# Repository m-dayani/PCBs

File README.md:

# PCBs

A collection of previous PCB designs

## CPLD Development Board

## Logic Circuits

### Logic Gates

### Combinational Logic

### Sequential Logic - Latch/FF

### Sequential Logic - SReg/Counter

## Miscellaneous

### Power Supply

### Tiny Oscilloscope

## Dependencies

These designs are tested using the following sotfware:

- Altium Designer 16.0.8 2015
- Eagle 7.6.0

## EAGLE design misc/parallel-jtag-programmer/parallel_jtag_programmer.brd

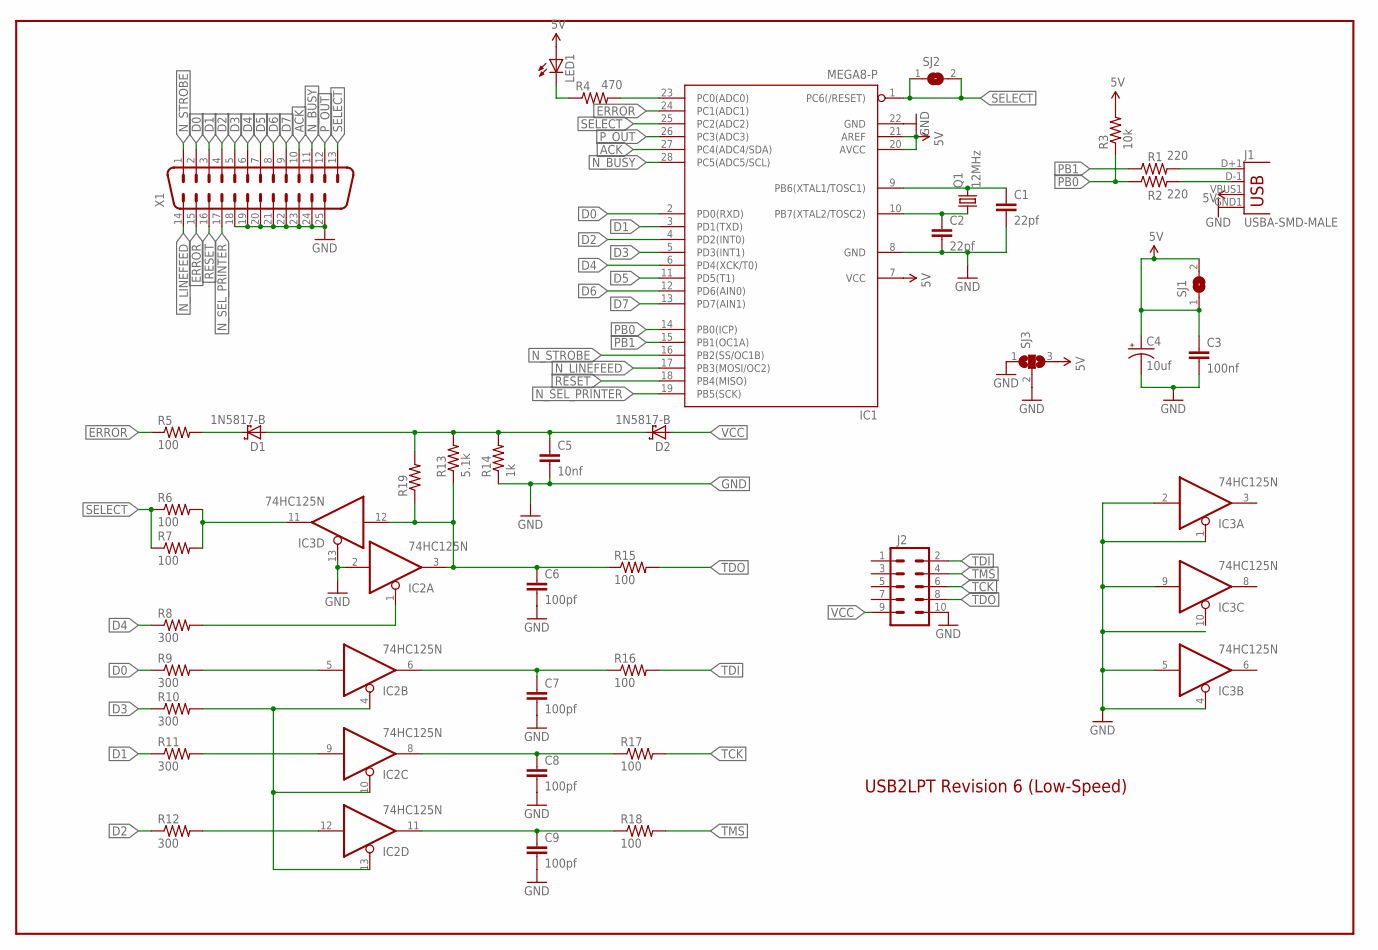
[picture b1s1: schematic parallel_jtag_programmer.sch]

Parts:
C1, C2: 22pf; CAP-PTH-SMALL
C3: 100nf; CAP-PTH-5MM
C4: 10uf; CPOL-RADIAL-10UF-25V
C5: 10nf; CAP-PTH-SMALL
C6, C7, C8, C9: 100pf; CAP-PTH-5MM
D1, D2: 1N5817-B; DO41-7.6
IC1: MEGA8-P; DIL28-3
IC2, IC3: 74HC125N; DIL14
J1: USBA-SMD-MALE; USB-A-SMT-MALE
J2: M05X2SHD; 2X5-SHROUDED
LED1: LED3MM
Q1: 12MHz; HC49U-V
R1, R2: 220; AXIAL-0.3
R3: 10k; AXIAL-0.3
R4: 470; AXIAL-0.3
R5, R6, R7, R15, R16, R17, R18: 100; AXIAL-0.3
R8, R9, R10, R11, R12: 300; AXIAL-0.3
R13: 5.1k; AXIAL-0.3
R14: 1k; AXIAL-0.3
R19: RESISTORAXIAL-0.3; AXIAL-0.3
SJ1, SJ2: SJ
SJ3: SJ2W; SJ_2
X1: DB25H; M25H

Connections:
5V: C3.1, C4.1 (+), IC1.7 (VCC), IC1.20 (AVCC), IC1.21 (AREF), J1.VBUS1 (VBUS), LED1.A, R3.P$2 (2), SJ1.1, SJ1.2, SJ3.3
ACK: IC1.27 (PC4(ADC4/SDA)), X1.10
D0: IC1.2 (PD0(RXD)), R9.P$1 (1), X1.2
D1: IC1.3 (PD1(TXD)), R11.P$1 (1), X1.3
D2: IC1.4 (PD2(INT0)), R12.P$1 (1), X1.4
D3: IC1.5 (PD3(INT1)), R10.P$1 (1), X1.5
D4: IC1.6 (PD4(XCK/T0)), R8.P$1 (1), X1.6
D5: IC1.11 (PD5(T1)), X1.7
D6: IC1.12 (PD6(AIN0)), X1.8
D7: IC1.13 (PD7(AIN1)), X1.9
ERROR: IC1.24 (PC1(ADC1)), R5.P$1 (1), X1.15
GND: C1.2, C2.2, C3.2, C4.2 (-), C5.2, C6.2, C7.2, C8.2, C9.2, IC1.8 (GND), IC1.22 (GND), IC2.2 (I), IC2.7 (GND), IC3.1 (OE), IC3.2 (I), IC3.4 (OE), IC3.5 (I), IC3.7 (GND), IC3.9 (I), IC3.13 (OE), J1.GND1 (GND), J2.10, R14.P$1 (1), SJ3.1, SJ3.2, X1.18, X1.19, X1.20, X1.21, X1.22, X1.23, X1.24, X1.25
unnamed: LED1.K (C), R4.P$1 (1)
unnamed: IC1.23 (PC0(ADC0)), R4.P$2 (2)
unnamed: C5.1, D1.A, D2.C, R13.P$2 (2), R14.P$2 (2), R19.P$2 (2)
unnamed: C2.1, IC1.10 (PB7(XTAL2/TOSC2)), Q1.1
unnamed: C1.1, IC1.9 (PB6(XTAL1/TOSC1)), Q1.2
unnamed: J1.D-1 (D-), R2.P$2 (2)
unnamed: J1.D+1 (D+), R1.P$2 (2)
unnamed: C6.1, IC2.3 (O), IC3.12 (I), R13.P$1 (1), R15.P$1 (1), R19.P$1 (1)
unnamed: IC2.1 (OE), R8.P$2 (2)
unnamed: IC3.11 (O), R6.P$2 (2), R7.P$2 (2)
unnamed: IC2.5 (I), R9.P$2 (2)
unnamed: IC2.4 (OE), IC2.10 (OE), IC2.13 (OE), R10.P$2 (2)
unnamed: D1.C, R5.P$2 (2)
unnamed: C7.1, IC2.6 (O), R16.P$1 (1)
unnamed: C8.1, IC2.8 (O), R17.P$1 (1)
unnamed: IC2.9 (I), R11.P$2 (2)
unnamed: IC2.12 (I), R12.P$2 (2)
unnamed: C9.1, IC2.11 (O), R18.P$1 (1)
N_BUSY: IC1.28 (PC5(ADC5/SCL)), X1.11
N_LINEFEED: IC1.17 (PB3(MOSI/OC2)), X1.14
N_SEL_PRINTER: IC1.19 (PB5(SCK)), X1.17
N_STROBE: IC1.16 (PB2(SS/OC1B)), X1.1
PB0: IC1.14 (PB0(ICP)), R2.P$1 (1), R3.P$1 (1)
PB1: IC1.15 (PB1(OC1A)), R1.P$1 (1)
P_OUT: IC1.26 (PC3(ADC3)), X1.12
RESET: IC1.18 (PB4(MISO)), X1.16
SELECT: IC1.1 (PC6(/RESET)), IC1.25 (PC2(ADC2)), R6.P$1 (1), R7.P$1 (1), SJ2.1, SJ2.2, X1.13
TCK: J2.6
TDI: J2.2, R16.P$2 (2)
TDO: J2.8, R15.P$2 (2)
TMS: J2.4, R18.P$2 (2)
VCC: D2.A, IC2.14 (VCC), IC3.14 (VCC), J2.9

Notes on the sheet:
USB2LPT Revision 6 (Low-Speed)

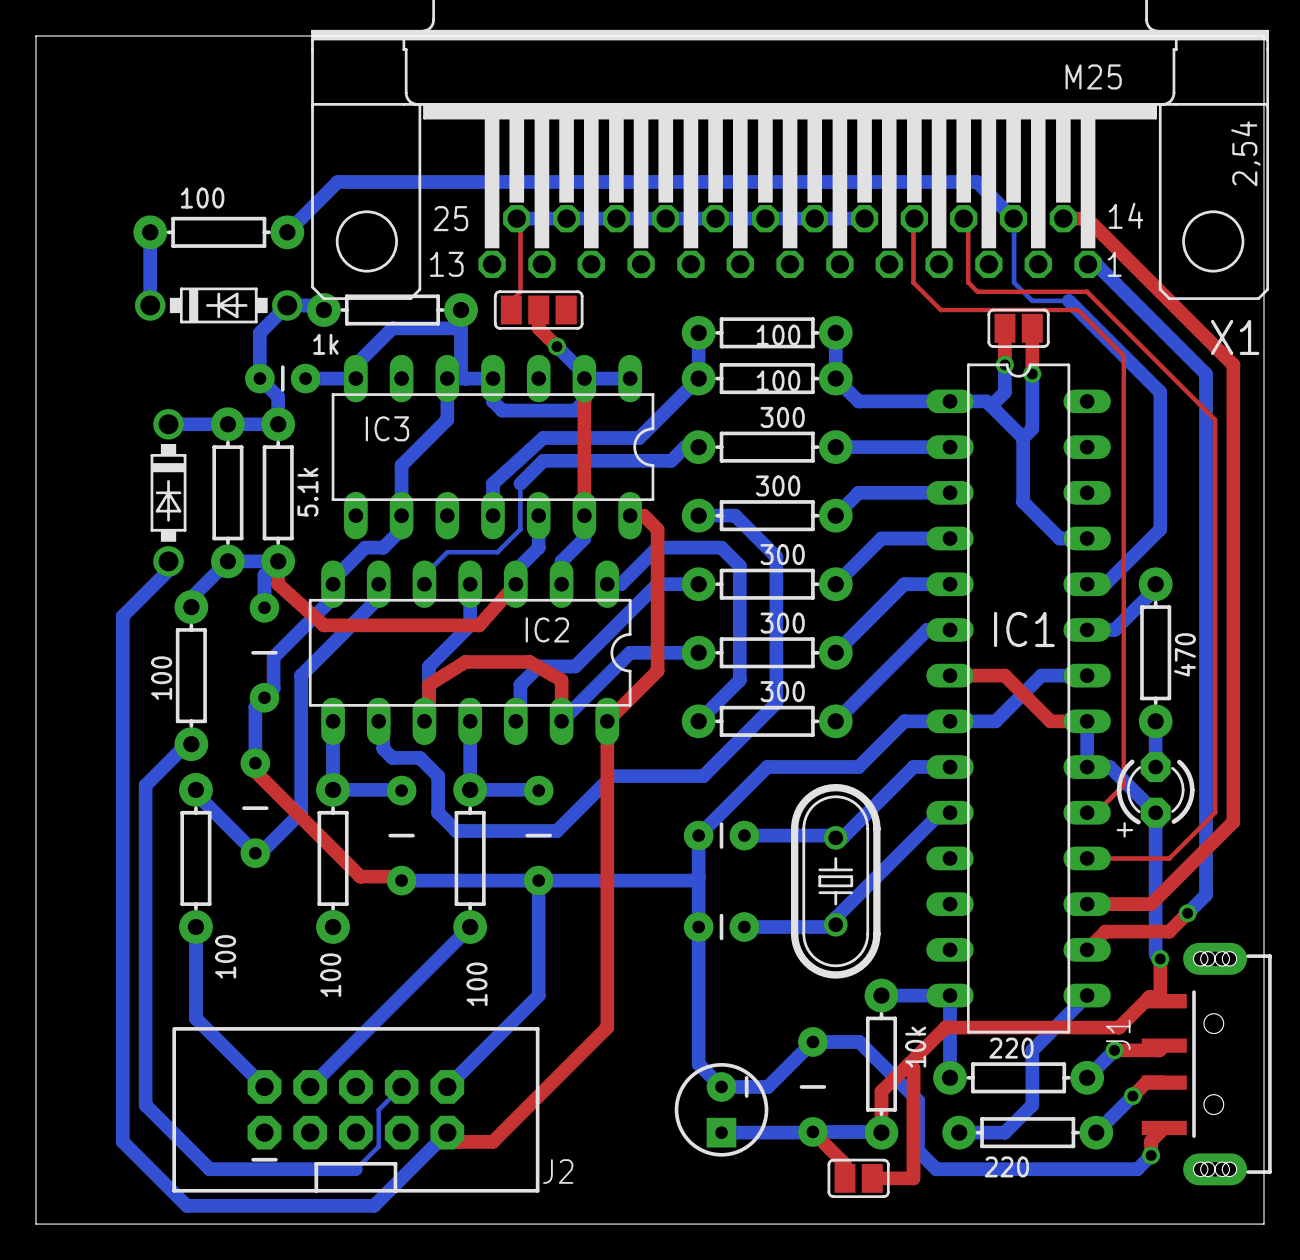
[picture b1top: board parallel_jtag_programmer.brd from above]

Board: 2 copper layers, 68.2 x 66.0 mm, 41 parts (0 on the bottom side), 43 nets.

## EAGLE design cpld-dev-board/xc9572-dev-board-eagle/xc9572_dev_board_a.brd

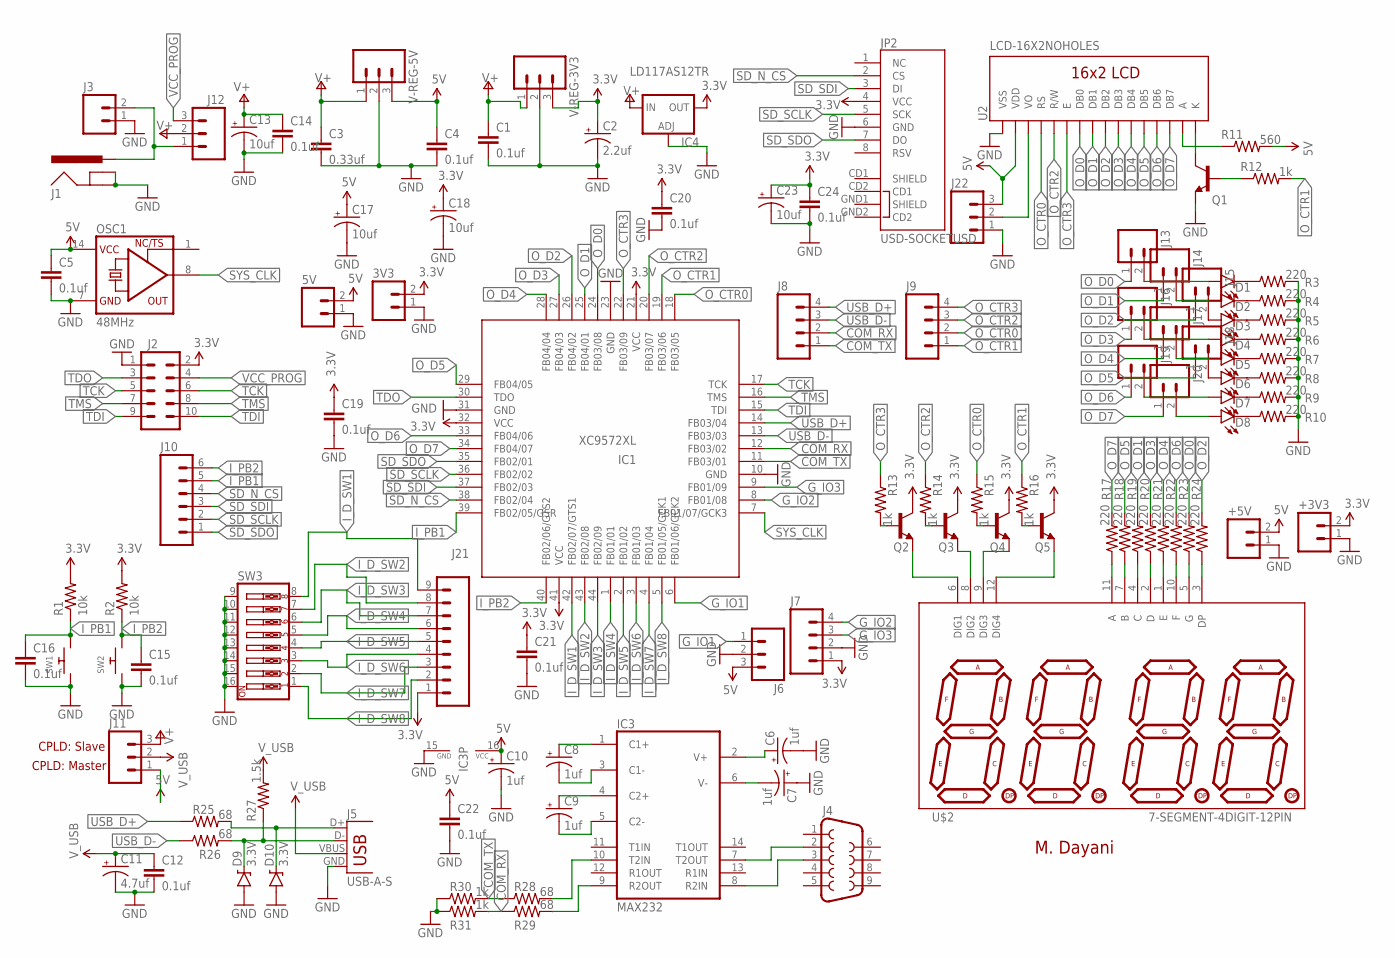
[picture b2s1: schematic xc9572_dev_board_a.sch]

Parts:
3V3, 5V: M02PTH; 1X02
+3V3, +5V: M02JST-PTH-VERT; JST-2-PTH-VERT
C1, C4, C5, C12, C14, C15, C16, C19, C20, C21, C22, C24: 0.1uf; 1206
C2: 2.2uf; EIA3216
C3: 0.33uf; 1206
C6, C7, C8, C9, C10: 1uf; EIA3216
C11: 4.7uf; EIA3216
C13, C17, C18, C23: 10uf; EIA3216
D1, D2, D3, D4, D5, D6, D7, D8: LED1206; LED-1206
D9, D10: 3.3V; SOD-323
IC1: XC9572XL; PLCC-S44
IC3: MAX232; DIL16
IC4: LD117AS12TR; SOT223
J1: POWER_JACKPTH_BREAD; POWER_JACK_PTH_BREAD
J2: M05X2SHD; 2X5-SHROUDED
J3: M02JST-PTH-VERT; JST-2-PTH-VERT
J4: DB9FEMALE; DB9
J5: USB-A-S
J6, J11, J12: M03PTH; 1X03
J7, J8, J9: M04PTH; 1X04
J10: M06SILK_FEMALE_PTH; 1X06
J13, J14, J15, J16, J17, J18, J19, J20: M02PTH; 1X02
J21: M09; 1X09
J22: M03POLAR; MOLEX-1X3
JP2: USD-SOCKETUSD; USD-SOCKET-PP
OSC1: 48MHz; DIL14S
Q1, Q2, Q3, Q4, Q5: TRANSISTOR_NPNSOT23-3; SOT23-3
R1, R2: 10k; 1206
R3, R4, R5, R6, R7, R8, R9, R10, R17, R18, R19, R20, R21, R22, R23, R24: 220; 1206
R11: 560; 1206
R12, R13, R14, R15, R16, R30, R31: 1k; 1206
R25, R26, R28, R29: 68; 1206
R27: 1.5k; 1206
SW1, SW2: SWITCH_PUSHBUTTONEVQ-PE; TACT_PANA-EVQ
SW3: SW_DIP-8; DIPSWITCH-08
U2: LCD-16X2NOHOLES; LCD-16X2_NOHOLES
U$2: 7-SEGMENT-4DIGIT-12PIN; 7-SEGMENT-4DIGIT-12PIN-LONGPADS
V-REG-3V3, V-REG-5V: M03PTH; 1X03

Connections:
3.3V: 3V3.2, +3V3.2, C2.A (+), C18.A (+), C19.1, C20.1, C21.1, C23.A (+), C24.1, IC1.21 (VCC), IC1.32 (VCC), IC1.41 (VCC), IC4.4 (OUT), J2.2, J7.1, J21.1, JP2.4 (VCC), Q2.3 (C), Q3.3 (C), Q4.3 (C), Q5.3 (C), R1.2, R2.2, V-REG-3V3.3
5V: 5V.2, +5V.2, C4.1, C5.1, C10.A (+), C17.A (+), C22.1, IC3.16 (VCC), J6.3, J11.1, J22.3, OSC1.14 (VCC), R11.2, U2.2 (VDD), V-REG-5V.3
COM_RX: IC1.12 (FB03/02), J8.2, R29.1, R31.2
COM_TX: IC1.11 (FB03/01), J8.1, R28.1, R30.2
GND: 3V3.1, 5V.1, +3V3.1, +5V.1, C1.2, C2.C (-), C3.2, C4.2, C5.2, C6.C (-), C7.A (+), C10.C (-), C11.C (-), C12.2, C13.C (-), C14.2, C15.2, C16.2, C17.C (-), C18.C (-), C19.2, C20.2, C21.2, C22.2, C23.C (-), C24.2, D9.A, D10.A, IC1.10 (GND), IC1.23 (GND), IC1.31 (GND), IC3.15 (GND), IC4.1 (ADJ), J1.GND, J1.GNDBREAK, J2.1, J3.1, J5.GND, J6.2, J7.2, J22.1, JP2.6 (GND), OSC1.7 (GND), Q1.2 (E), R3.2, R4.2, R5.2, R6.2, R7.2, R8.2, R9.2, R10.2, R30.1, R31.1, SW1.P$1, SW2.P$1, SW3.9, SW3.10, SW3.11, SW3.12, SW3.13, SW3.14, SW3.15, SW3.16, U2.1 (VSS), V-REG-3V3.2, V-REG-5V.2
G_IO1: IC1.6 (FB01/06/GCK2), J6.1
G_IO2: IC1.8 (FB01/08), J7.4
G_IO3: IC1.9 (FB01/09), J7.3
I_D_SW1: IC1.42 (FB02/07/GTS1), J21.9, SW3.8
I_D_SW2: IC1.43 (FB02/08), J21.8, SW3.7
I_D_SW3: IC1.44 (FB02/09), J21.7, SW3.6
I_D_SW4: IC1.1 (FB01/01), J21.6, SW3.5
I_D_SW5: IC1.2 (FB01/02), J21.5, SW3.4
I_D_SW6: IC1.3 (FB01/03), J21.4, SW3.3
I_D_SW7: IC1.4 (FB01/04), J21.3, SW3.2
I_D_SW8: IC1.5 (FB01/05/GCK1), J21.2, SW3.1
I_PB1: C16.1, IC1.39 (FB02/05/GSR), J10.5, R1.1, SW1.P$2
I_PB2: C15.1, IC1.40 (FB02/06/GTS2), J10.6, R2.1, SW2.P$2
unnamed: D3.A, J15.2
unnamed: D6.A, J18.2
unnamed: D8.A, J20.2
unnamed: D7.A, J19.2
unnamed: D5.A, J17.2
unnamed: D4.A, J16.2
unnamed: D2.A, J14.2
unnamed: D1.A, J13.2
unnamed: D8.C, R10.1
unnamed: D7.C, R9.1
unnamed: D6.C, R8.1
unnamed: D5.C, R7.1
unnamed: D4.C, R6.1
unnamed: D3.C, R5.1
unnamed: D2.C, R4.1
unnamed: D1.C, R3.1
unnamed: J22.2, U2.3 (VO)
unnamed: Q1.3 (C), U2.16 (K)
unnamed: R11.1, U2.15 (A)
unnamed: Q1.1 (B), R12.1
unnamed: Q2.1 (B), R13.2
unnamed: Q3.1 (B), R14.2
unnamed: Q4.1 (B), R15.2
unnamed: Q5.1 (B), R16.2
unnamed: Q2.2 (E), U$2.6 (DIG1)
unnamed: Q3.2 (E), U$2.8 (DIG2)
unnamed: Q4.2 (E), U$2.9 (DIG3)
unnamed: Q5.2 (E), U$2.12 (DIG4)
unnamed: R17.1, U$2.11 (A)
unnamed: R18.1, U$2.7 (B)
unnamed: R19.1, U$2.4 (C)
unnamed: R20.1, U$2.2 (D)
unnamed: R21.1, U$2.1 (E)
unnamed: R22.1, U$2.10 (F)
unnamed: R23.1, U$2.5 (G)
unnamed: R24.1, U$2.3 (DP)
unnamed: IC3.7 (T2OUT), J4.2
unnamed: IC3.8 (R2IN), J4.3
unnamed: C7.C (-), IC3.6 (V-)
unnamed: C6.A (+), IC3.2 (V+)
unnamed: C8.A (+), IC3.1 (C1+)
unnamed: C8.C (-), IC3.3 (C1-)
unnamed: C9.A (+), IC3.4 (C2+)
unnamed: C9.C (-), IC3.5 (C2-)
unnamed: D9.C, J5.D-, R26.2, R27.1
unnamed: D10.C, J5.D+, R25.2
unnamed: IC3.10 (T2IN), R28.2
unnamed: IC3.9 (R2OUT), R29.2
O_CTR0: IC1.18 (FB03/05), J9.2, R15.1, U2.4 (RS)
O_CTR1: IC1.19 (FB03/06), J9.1, R12.2, R16.1
O_CTR2: IC1.20 (FB03/07), J9.3, R14.1, U2.5 (R/W)
O_CTR3: IC1.22 (FB03/09), J9.4, R13.1, U2.6 (E)
O_D0: IC1.24 (FB03/08), J13.1, R23.2, U2.7 (DB0)
O_D1: IC1.25 (FB04/01), J14.1, R19.2, U2.8 (DB1)
O_D2: IC1.26 (FB04/02), J15.1, R24.2, U2.9 (DB2)
O_D3: IC1.27 (FB04/03), J16.1, R20.2, U2.10 (DB3)
O_D4: IC1.28 (FB04/04), J17.1, R21.2, U2.11 (DB4)
O_D5: IC1.29 (FB04/05), J18.1, R18.2, U2.12 (DB5)
O_D6: IC1.33 (FB04/06), J19.1, R22.2, U2.13 (DB6)
O_D7: IC1.34 (FB04/07), J20.1, R17.2, U2.14 (DB7)
SD_N_CS: IC1.38 (FB02/04), J10.4, JP2.2 (CS)
SD_SCLK: IC1.36 (FB02/02), J10.2, JP2.5 (SCK)
SD_SDI: IC1.37 (FB02/03), J10.3, JP2.3 (DI)
SD_SDO: IC1.35 (FB02/01), J10.1, JP2.7 (DO)
SYS_CLK: IC1.7 (FB01/07/GCK3), OSC1.8 (OUT)
TCK: IC1.17 (TCK), J2.5, J2.6
TDI: IC1.15 (TDI), J2.9, J2.10
TDO: IC1.30 (TDO), J2.3
TMS: IC1.16 (TMS), J2.7, J2.8
USB_D+: IC1.14 (FB03/04), J8.4, R25.1
USB_D-: IC1.13 (FB03/03), J8.3, R26.1
V+: C1.1, C3.1, C13.A (+), C14.1, IC4.3 (IN), J11.3, J12.2, V-REG-3V3.1, V-REG-5V.1
VCC_PROG: J2.4, J12.3
V_IN: J1.PWR, J3.2, J12.1
V_USB: C11.A (+), C12.1, J5.VBUS, J11.2, R27.2

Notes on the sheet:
M. Dayani
CPLD: Slave
CPLD: Master

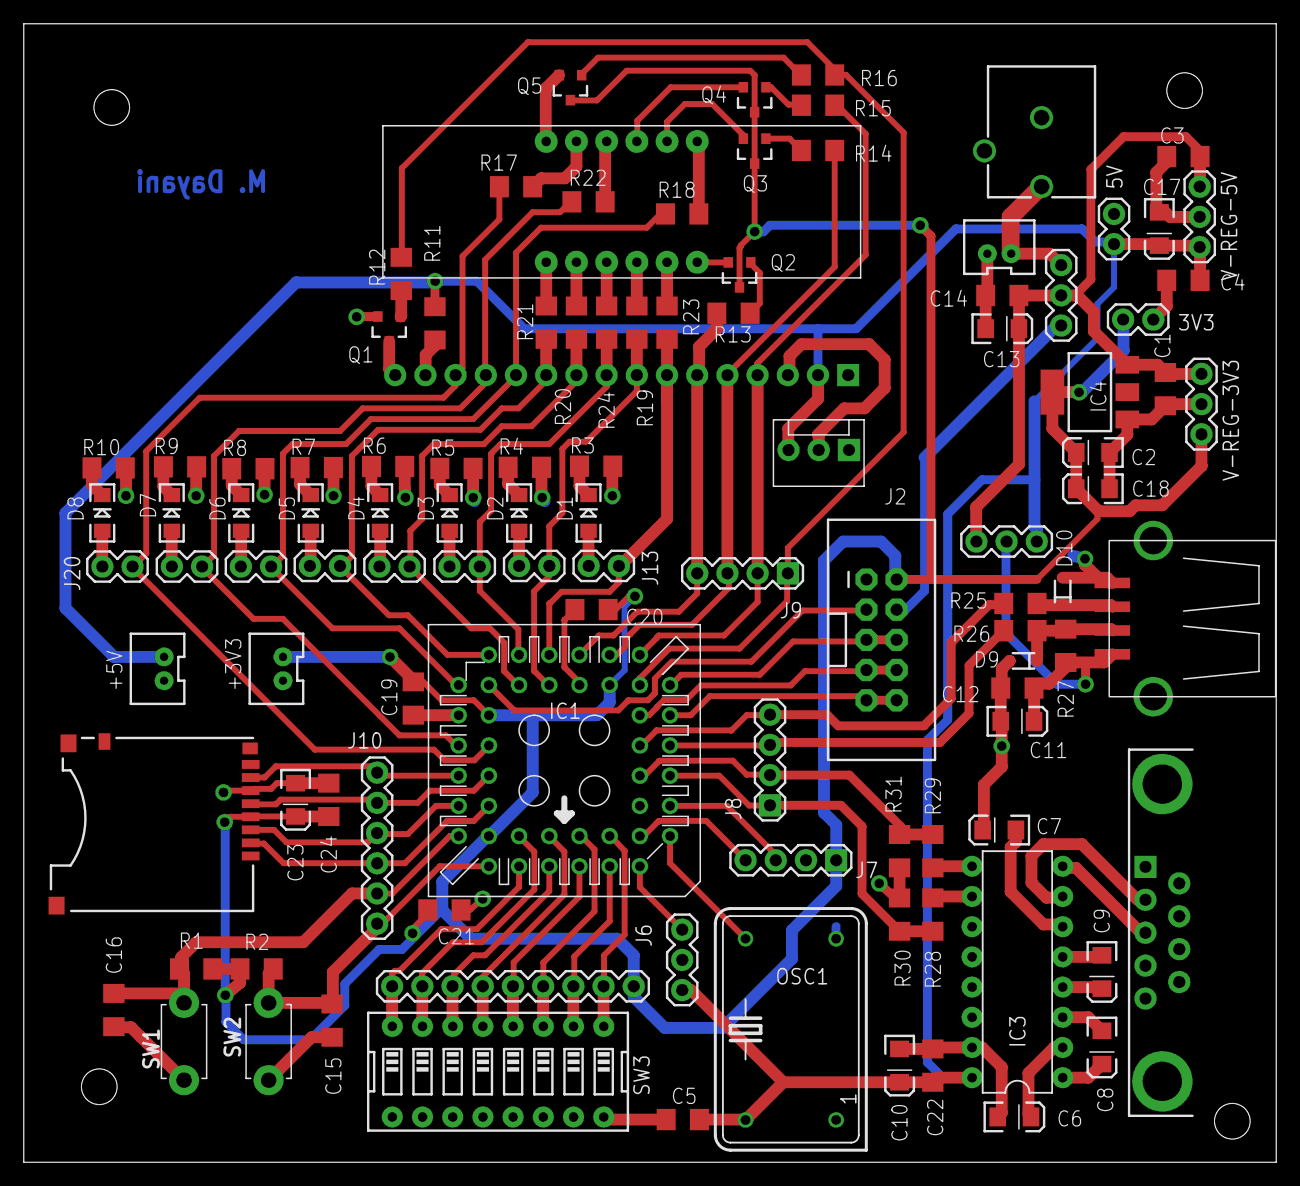
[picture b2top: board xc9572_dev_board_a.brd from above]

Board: 2 copper layers, 105.3 x 95.7 mm, 108 parts (0 on the bottom side), 93 nets.

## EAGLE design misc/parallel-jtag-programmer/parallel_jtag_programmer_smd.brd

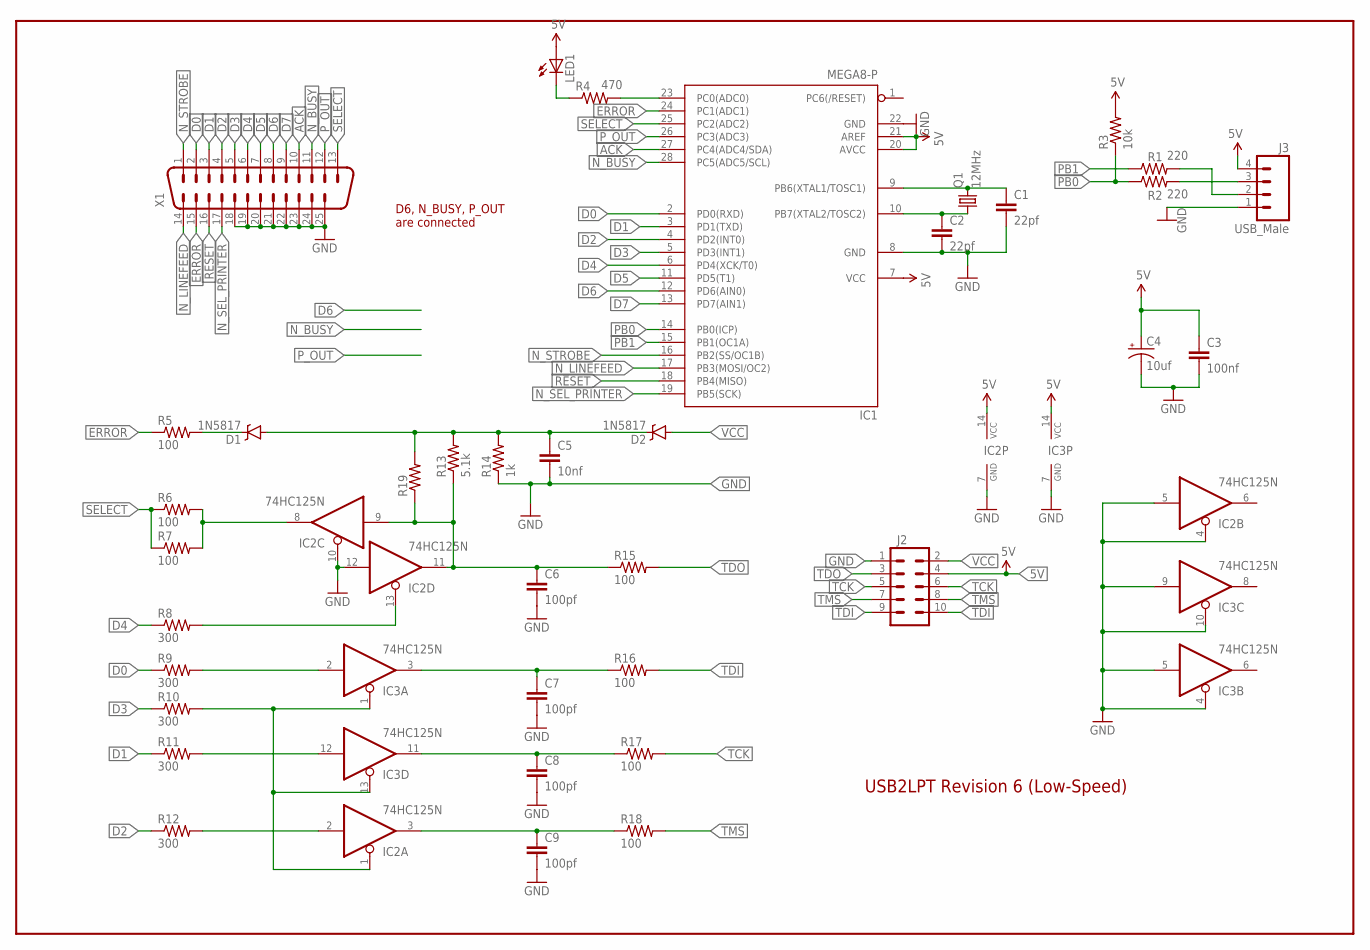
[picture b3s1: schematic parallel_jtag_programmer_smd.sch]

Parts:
C1, C2: 22pf; CAP-PTH-SMALL
C3: 100nf; 1206
C4: 10uf; EIA3216
C5: 10nf; 1206
C6, C7, C8, C9: 100pf; 1206
D1, D2: 1N5817; SMA-DIODE
IC1: MEGA8-P; DIL28-3
IC2, IC3: 74HC125N; DIL14
J2: M05X2SHD; 2X5-SHROUDED
J3: USB_Male; 1X04
LED1: LED3MM
Q1: 12MHz; HC49U-V
R1, R2: 220; 1206
R3: 10k; 1206
R4: 470; 1206
R5, R6, R7, R15, R16, R17, R18: 100; 1206
R8, R9, R10, R11, R12: 300; 1206
R13: 5.1k; 1206
R14: 1k; 1206
R19: RESISTOR1206; 1206
X1: DB25D; M25D

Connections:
5V: C3.1, C4.A (+), IC1.7 (VCC), IC1.20 (AVCC), IC1.21 (AREF), IC2.14 (VCC), IC3.14 (VCC), J2.4, J3.4, LED1.A, R3.2
ACK: IC1.27 (PC4(ADC4/SDA)), X1.10
D0: IC1.2 (PD0(RXD)), R9.1, X1.2
D1: IC1.3 (PD1(TXD)), R11.1, X1.3
D2: IC1.4 (PD2(INT0)), R12.1, X1.4
D3: IC1.5 (PD3(INT1)), R10.1, X1.5
D4: IC1.6 (PD4(XCK/T0)), R8.1, X1.6
D5: IC1.11 (PD5(T1)), X1.7
D6: IC1.12 (PD6(AIN0)), X1.8
D7: IC1.13 (PD7(AIN1)), X1.9
ERROR: IC1.24 (PC1(ADC1)), R5.1, X1.15
GND: C1.2, C2.2, C3.2, C4.C (-), C5.2, C6.2, C7.2, C8.2, C9.2, IC1.8 (GND), IC1.22 (GND), IC2.4 (OE), IC2.5 (I), IC2.7 (GND), IC2.10 (OE), IC2.12 (I), IC3.4 (OE), IC3.5 (I), IC3.7 (GND), IC3.9 (I), IC3.10 (OE), J2.1, J3.1, R14.1, X1.18, X1.19, X1.20, X1.21, X1.22, X1.23, X1.24, X1.25
unnamed: LED1.K (C), R4.1
unnamed: IC1.23 (PC0(ADC0)), R4.2
unnamed: C5.1, D1.A, D2.C, R13.2, R14.2, R19.2
unnamed: C2.1, IC1.10 (PB7(XTAL2/TOSC2)), Q1.1
unnamed: C1.1, IC1.9 (PB6(XTAL1/TOSC1)), Q1.2
unnamed: J3.3, R2.2
unnamed: C6.1, IC2.9 (I), IC2.11 (O), R13.1, R15.1, R19.1
unnamed: IC2.13 (OE), R8.2
unnamed: IC2.8 (O), R6.2, R7.2
unnamed: J3.2, R1.2
unnamed: IC3.2 (I), R9.2
unnamed: IC2.1 (OE), IC3.1 (OE), IC3.13 (OE), R10.2
unnamed: D1.C, R5.2
unnamed: C7.1, IC3.3 (O), R16.1
unnamed: C8.1, IC3.11 (O), R17.1
unnamed: IC3.12 (I), R11.2
unnamed: IC2.2 (I), R12.2
unnamed: C9.1, IC2.3 (O), R18.1
N_BUSY: IC1.28 (PC5(ADC5/SCL)), X1.11
N_LINEFEED: IC1.17 (PB3(MOSI/OC2)), X1.14
N_SEL_PRINTER: IC1.19 (PB5(SCK)), X1.17
N_STROBE: IC1.16 (PB2(SS/OC1B)), X1.1
PB0: IC1.14 (PB0(ICP)), R2.1, R3.1
PB1: IC1.15 (PB1(OC1A)), R1.1
P_OUT: IC1.26 (PC3(ADC3)), X1.12
RESET: IC1.18 (PB4(MISO)), X1.16
SELECT: IC1.25 (PC2(ADC2)), R6.1, R7.1, X1.13
TCK: J2.5, J2.6, R17.2
TDI: J2.9, J2.10, R16.2
TDO: J2.3, R15.2
TMS: J2.7, J2.8, R18.2
VCC: D2.A, J2.2

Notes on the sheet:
USB2LPT Revision 6 (Low-Speed)
D6, N_BUSY, P_OUT are connected

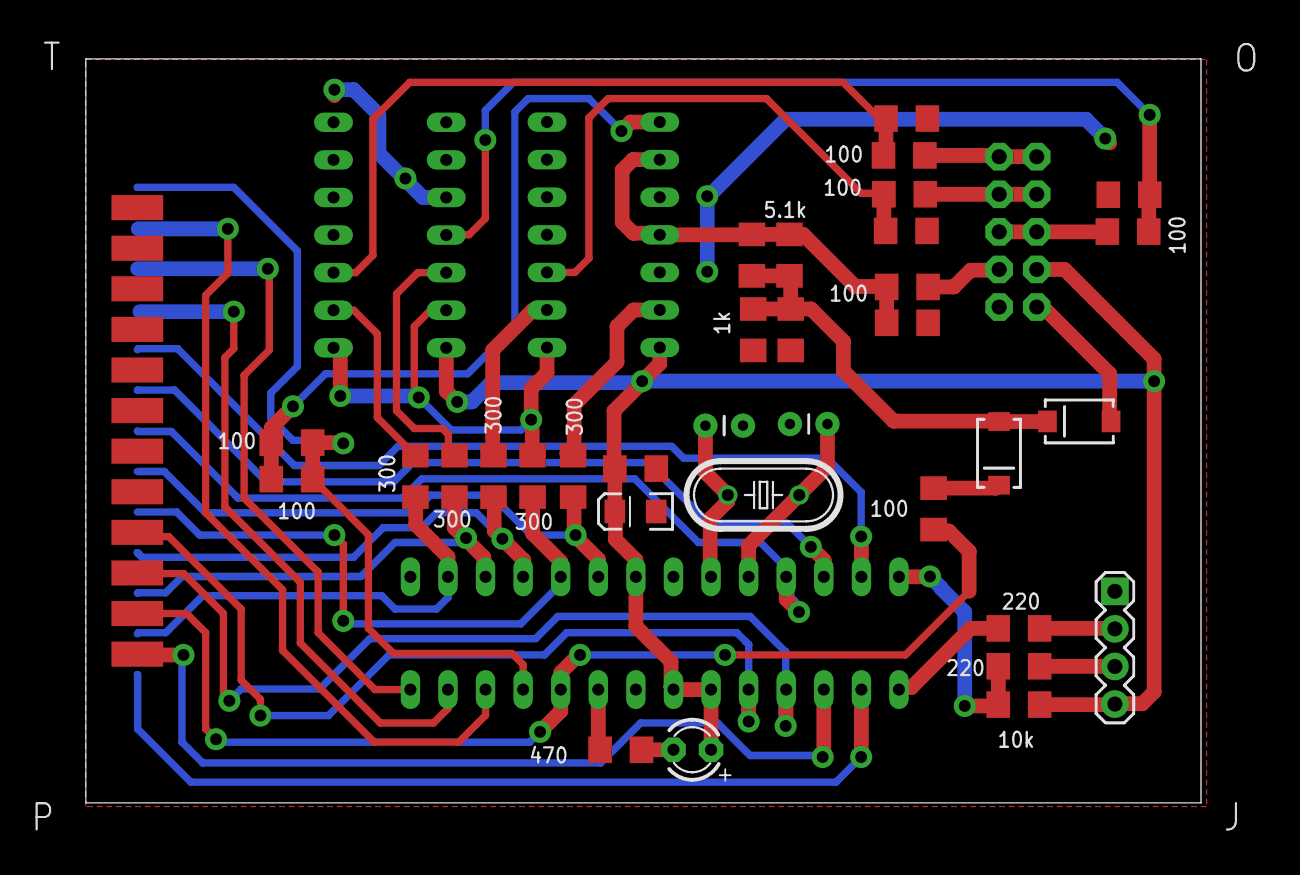
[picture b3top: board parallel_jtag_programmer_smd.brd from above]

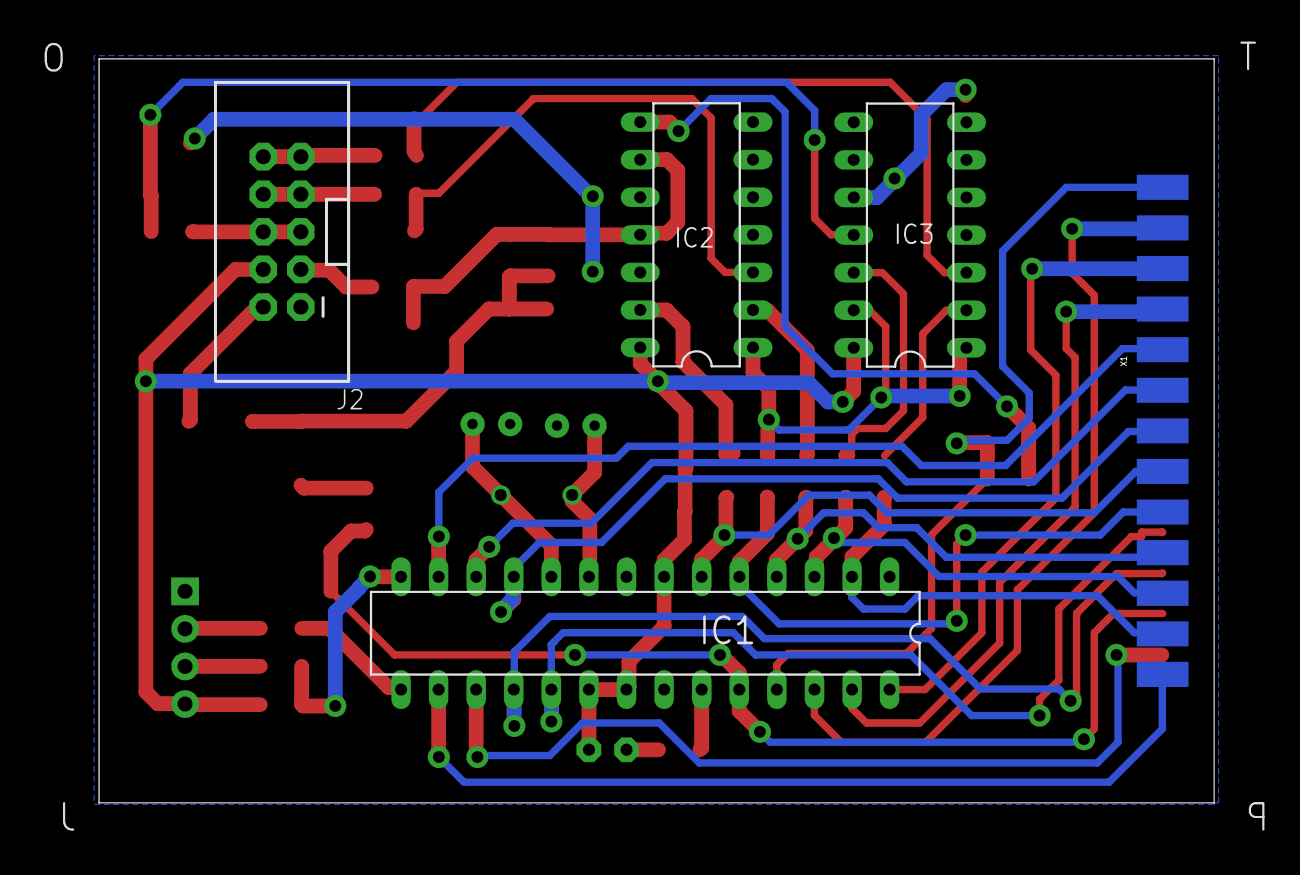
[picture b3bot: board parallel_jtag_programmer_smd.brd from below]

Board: 2 copper layers, 83.9 x 55.1 mm, 38 parts (5 on the bottom side), 44 nets.

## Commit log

2024-05-07 a collection of some of my PCB designs
2024-06-12 added image to readme.md
2024-07-03 modified readme.md

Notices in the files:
parts and their libraries:
SparkFun-Passives: Licensing: Creative Commons ShareAlike 4.0 International - https://creativecommons.org/licenses/by-sa/4.0
